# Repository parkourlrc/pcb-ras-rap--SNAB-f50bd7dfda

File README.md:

# README and whole project is still being worked on

---

# Switch iN A Bottle (SNAB)

SNAB is a protable device that allows you to take full control of your switch.

## What does this do?

- RCM payload injection
- Bluetooth gamepad dongle
- Charge monitoring
- Maybe more

## Why did you make this?

My switch dies quite often when I travel, and I dont always have some kind of computer avalible, and I use an iPhone so I cant use my phone. Also I wanted to learn how the Fusee Gelee exploit works and how to design hardware projects.

## Why not buy a commecial product on Amazon?

There's nothing stopping you from doing that, but sometimes it's more fun to do it yourself, plus you learn something along the way.

## Bill Of Materials

The full bill of materials is avalible at [BOM.csv](../blob/main/BOM.csv) but make sure to read this first

There are a couple of parts from AliExpress that there are specific versions needed, or atleast expected

| Name        | Link           | Model  |
| ------------|:--------------| ------|
|Battery Charger      | [AliExpress](https://www.aliexpress.us/item/3256807978024318.html) | MH-CD42 Upgraded |
| Battery | [AliExpress](https://www.aliexpress.us/item/3256811659050819.html)      |  1 pc   |
| Screen      | [AliExpress](https://www.aliexpress.us/item/3256807856044374.html)      |  1.8 inch TFT  |
| ESP 32 Dev Board | [AliExpress](https://www.aliexpress.us/item/3256808564662702.html)      |    ESP32-S3-N8R2 |

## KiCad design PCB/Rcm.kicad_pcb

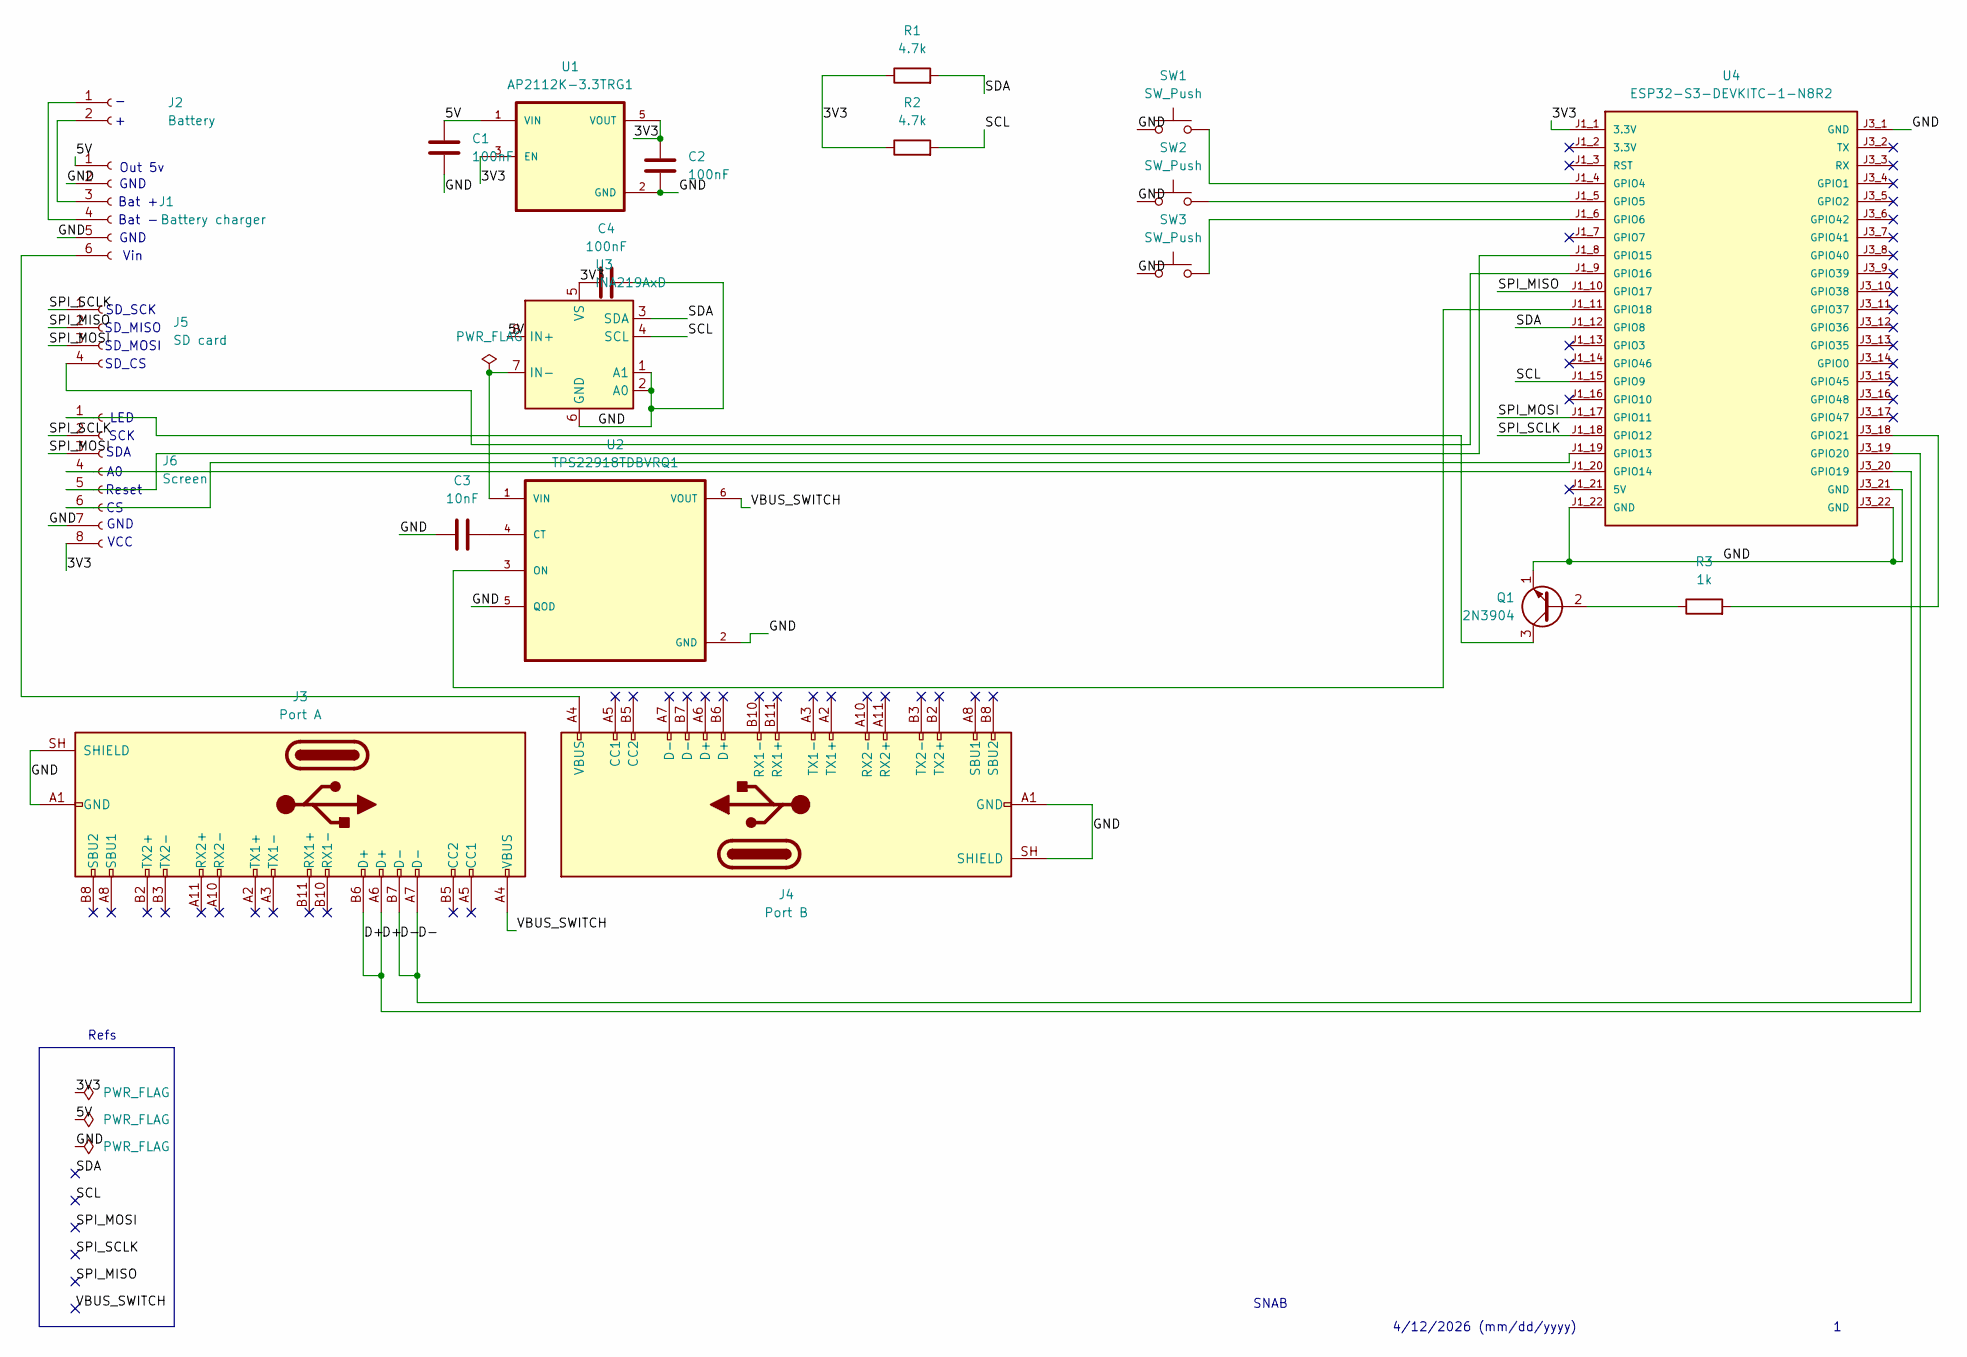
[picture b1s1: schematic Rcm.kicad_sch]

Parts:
C1, C2, C4: 100nF; C_Disc_D10.0mm_W2.5mm_P5.00mm
C3: 10nF; C_Disc_D10.0mm_W2.5mm_P5.00mm
J1: Battery charger; PinSocket_1x06_P2.54mm_Vertical
J2: Battery; JST_PH_B2B-PH-K_1x02_P2.00mm_Vertical
J3: Port A; USB_C_Receptacle_GCT_USB4085
J4: Port B; USB_C_Receptacle_GCT_USB4085
J5: SD card; PinSocket_1x04_P2.54mm_Vertical
J6: Screen; PinSocket_1x08_P2.54mm_Vertical
Q1: 2N3904; TO-92_Inline
R1, R2: 4.7k; R_Axial_DIN0204_L3.6mm_D1.6mm_P5.08mm_Vertical
R3: 1k; R_Axial_DIN0204_L3.6mm_D1.6mm_P5.08mm_Vertical
SW1, SW2, SW3: SW_Push; SW_PUSH_6mm_H7.3mm
U1: AP2112K-3.3TRG1; SOT95P285X140-5N; PARTREV 2-2
U2: TPS22918TDBVRQ1; SOT95P280X145-6N
U3: INA219AxD; SOIC-8_3.9x4.9mm_P1.27mm
U4: ESP32-S3-DEVKITC-1-N8R2; XCVR_ESP32-S3-DEVKITC-1-N8R2; PARTREV V1

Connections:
/3V3: C2.1, C4.2, J6.8, R1.1, R2.1, U1.3 (EN), U1.5 (VOUT), U3.5 (VS), U4.J1_1 (3.3V)
/5V: C1.1, J1.1, U1.1 (VIN), U3.8 (IN+)
/D+: J3.A6 (D+), J3.B6 (D+), U4.J3_19 (GPIO20)
/D-: J3.A7 (D-), J3.B7 (D-), U4.J3_20 (GPIO19)
/GND: C1.2, C2.2, C3.1, C4.1, J1.2, J1.5, J3.A1 (GND), J3.A12 (GND), J3.B1 (GND), J3.B12 (GND), J3.SH (SHIELD), J4.A1 (GND), J4.A12 (GND), J4.B1 (GND), J4.B12 (GND), J4.SH (SHIELD), J6.7, Q1.1 (E), SW1.1, SW2.1, SW3.1, U1.2 (GND), U2.2 (GND), U2.5 (QOD), U3.1 (A1), U3.2 (A0), U3.6 (GND), U4.J1_22 (GND), U4.J3_1 (GND), U4.J3_21 (GND), U4.J3_22 (GND)
/SCL: R2.2, U3.4 (SCL), U4.J1_15 (GPIO9)
/SDA: R1.2, U3.3 (SDA), U4.J1_12 (GPIO8)
/SPI_MISO: J5.2, U4.J1_10 (GPIO17)
/SPI_MOSI: J5.3, J6.3, U4.J1_17 (GPIO11)
/SPI_SCLK: J5.1, J6.2, U4.J1_18 (GPIO12)
/VBUS_SWITCH: J3.A4 (VBUS), J3.A9 (VBUS), J3.B4 (VBUS), J3.B9 (VBUS), U2.6 (VOUT)
unnamed: J1.3, J2.2
unnamed: J1.4, J2.1
unnamed: J1.6, J4.A4 (VBUS), J4.A9 (VBUS), J4.B4 (VBUS), J4.B9 (VBUS)
unnamed: J5.4, U4.J1_9 (GPIO16)
unnamed: J6.1, Q1.3 (C)
unnamed: J6.4, U4.J1_20 (GPIO14)
unnamed: J6.5, U4.J1_8 (GPIO15)
unnamed: J6.6, U4.J1_19 (GPIO13)
unnamed: Q1.2 (B), R3.1
unnamed: C3.2, U2.4 (CT)
unnamed: U2.3 (ON), U4.J1_11 (GPIO18)
unnamed: U2.1 (VIN), U3.7 (IN-)
unnamed: SW1.2, U4.J1_4 (GPIO4)
unnamed: SW2.2, U4.J1_5 (GPIO5)
unnamed: SW3.2, U4.J1_6 (GPIO6)
unnamed: R3.2, U4.J3_18 (GPIO21)

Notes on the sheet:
4/12/2026 (mm/dd/yyyy)
GND
Bat +
SD_SCK
Out 5v
LED
VCC
SD_CS
GND
Bat -
Reset
SNAB
SD_MOSI
Refs
SDA
SD_MISO
Vin
SCK

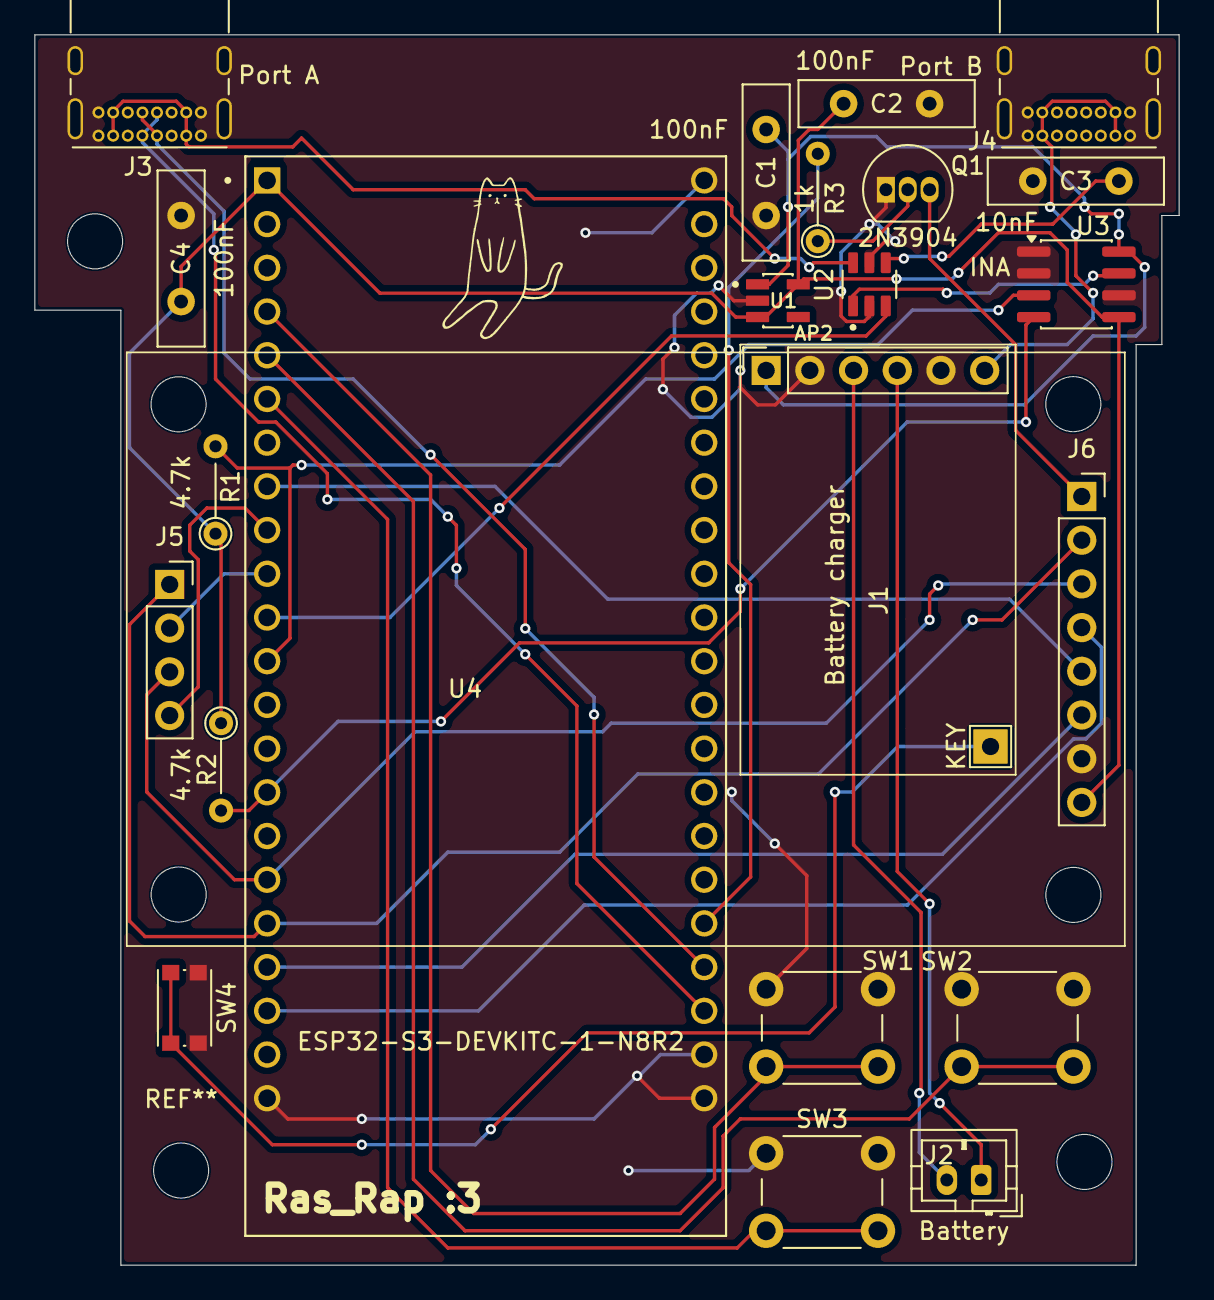
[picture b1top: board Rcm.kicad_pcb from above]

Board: 2 copper layers, 66.5 x 71.5 mm, 21 parts (0 on the bottom side), 27 nets.

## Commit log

2026-04-10 Create git repo and add pcb files
2026-04-10 Add LICENSE
2026-04-11 Session 2
2026-04-12 Session 3, created the schematic
2026-04-12 Add .gitignore
2026-04-12 Created README, BOM.csv, and a couple other things
2026-04-12 Created PCB, updated BOM, and I might have done something else
2026-04-16 Did a lot, been a while since I commited
